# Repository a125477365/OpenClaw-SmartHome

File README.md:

# OpenClaw Smart Home System

## Overview

This repository provides a complete design for a smart home system built on the OpenClaw platform. It consists of:

- **1 Skill**: `HomeSkill` (container for plugins)
- **2 Plugins**:
  1. `DeviceLinkPlugin` – handles device connection, ECDH pairing, encryption, control, and status reporting
  2. `UIManagePlugin` – provides a web-based management interface (HTTPS with password auth, auto port selection)
- **1 Data file**: `devices.json` – stores device info, state, and encryption keys
- **Hardware design**: ESP32-based smart switch

All code and documentation are in English.

## Security Features

### ECDH-Based Pairing (Bluetooth-Style)

- **No pre-shared secrets**: Each device generates its own EC key pair
- **User confirmation**: 6-digit confirmation code prevents MITM attacks
- **Forward secrecy**: New session keys for each pairing
- **AES-256-GCM encryption**: Authenticated encryption for all communications

### UI Security

- **Password protected**: Strong password required for web access
- **HTTPS only**: HTTP redirects to HTTPS
- **Session management**: 24-hour session timeout
- **Password hashing**: PBKDF2-SHA512 with 100,000 iterations

## Directory Structure

```
OpenClaw-SmartHome/
├── README.md
├── Skills/
│   └── HomeSkill/
│       ├── openclaw.skill.json
│       ├── package.json              # npm dependencies
│       ├── devices.json
│       ├── DeviceLinkPlugin/
│       │   ├── openclaw.plugin.json
│       │   ├── config.json
│       │   └── index.js              # Main plugin code
│       └── UIManagePlugin/
│           ├── openclaw.plugin.json
│           ├── config.json
│           ├── index.js              # HTTPS server
│           ├── password.json         # Stored password hash
│           ├── ssl/
│           │   ├── cert.pem
│           │   └── key.pem
│           └── web/
│               ├── index.html
│               └── edit.html
├── docs/
│   ├── hardware-design.md
│   ├── security-design.md
│   └── software-design.md
└── firmware/
    └── esp32_switch/
        └── esp32_switch.ino
```

## Tools Provided

### DeviceLinkPlugin

| Tool | Description |
|------|-------------|
| `device.control` | Send control command (on/off/query) |
| `device.pairing.start` | Initiate ECDH pairing process |
| `device.pairing.confirm` | Complete pairing after user confirms code |
| `device.pairing.reject` | Reject pending pairing |
| `device.reconnect` | Reconnect using stored public key |
| `device.unauthorize` | Revoke device authorization |
| `device.delete` | Remove device completely |
| `device.sync` | Query and update device state |
| `device.list` | List all registered devices |

### UIManagePlugin

| Tool | Description |
|------|-------------|
| `ui.password.get` | Get password info (cannot view, only reset) |
| `ui.password.reset` | Generate new random password |
| `ui.ports` | Get actual HTTP/HTTPS ports in use |

## Configuration

### Auto Port Selection

Both plugins support automatic port selection:

1. Tries configured port first
2. If occupied, searches for next available port
3. Search range configurable via `portRangeMin` and `portRangeMax`

### DeviceLinkPlugin/config.json

```json
{
  "devicePort": 8080,
  "mdnsPort": 5353,
  "pairingTimeout": 60000,
  "portRangeMin": 8080,
  "portRangeMax": 8100,
  "enableMdnsDiscovery": false,
  "encryption": {
    "algorithm": "aes-256-gcm",
    "keyLength": 32,
    "ivLength": 12
  }
}
```

### UIManagePlugin/config.json

```json
{
  "httpsPort": 8083,
  "httpPort": 8082,
  "portRangeMin": 8080,
  "portRangeMax": 8100,
  "webRoot": "./web",
  "ssl": {
    "key": "./ssl/key.pem",
    "cert": "./ssl/cert.pem"
  }
}
```

## Quick Start

1. Clone this repository into your OpenClaw `Skills/` directory:
   ```bash
   git clone https://github.com/your-org/OpenClaw-SmartHome.git ~/.openclaw/skills/HomeSkill
   ```

2. Install dependencies:
   ```bash
   cd ~/.openclaw/skills/HomeSkill
   npm install
   ```

3. Restart OpenClaw (skills load automatically)

4. Access the UI:
   - HTTPS: `https://localhost:8083` (or next available port)
   - Check logs for initial password: `ui.password.reset` to get a new one

5. Pair a device:
   ```
   User: I found a new device, start pairing
   Agent: [calls device.pairing.start]
   Agent: Please confirm code 123456 matches the device
   User: Confirmed
   Agent: [calls device.pairing.confirm]
   ```

## Pairing Flow

```
┌─────────────┐                    ┌─────────────┐
│   Device    │                    │  OpenClaw   │
└──────┬──────┘                    └──────┬──────┘
       │                                  │
       │ pairing_request                  │
       │ {deviceId, publicKey}            │
       │─────────────────────────────────>│
       │                                  │
       │                Compute shared secret
       │                Generate 6-digit code
       │                                  │
       │ pairing_response                 │
       │ {ephemeralPublicKey, salt}       │
       │<─────────────────────────────────│
       │                                  │
       │    [User confirms code matches]  │
       │                                  │
       │ pairing_confirm                  │
       │ {confirmed: true}                │
       │─────────────────────────────────>│
       │                                  │
       │ pairing_success                  │
       │<─────────────────────────────────│
       │                                  │
```

## Hardware Design

See `docs/hardware-design.md` for:
- ESP32-WROOM-32D based smart switch
- Relay module (5V, opto-isolated)
- PCB layout and BOM
- Assembly instructions

## Security Design

See `docs/security-design.md` for:
- ECDH pairing details
- AES-256-GCM encryption
- Replay attack protection
- Production security recommendations

## Software Design

See `docs/software-design.md` for:
- Architecture diagrams
- Communication protocol
- API specifications
- Data structures

## Firmware

See `firmware/esp32_switch/esp32_switch.ino` for:
- ESP32 Arduino firmware
- ECDH key generation
- AES-256-GCM encryption
- WiFi SmartConfig provisioning

## License

MIT

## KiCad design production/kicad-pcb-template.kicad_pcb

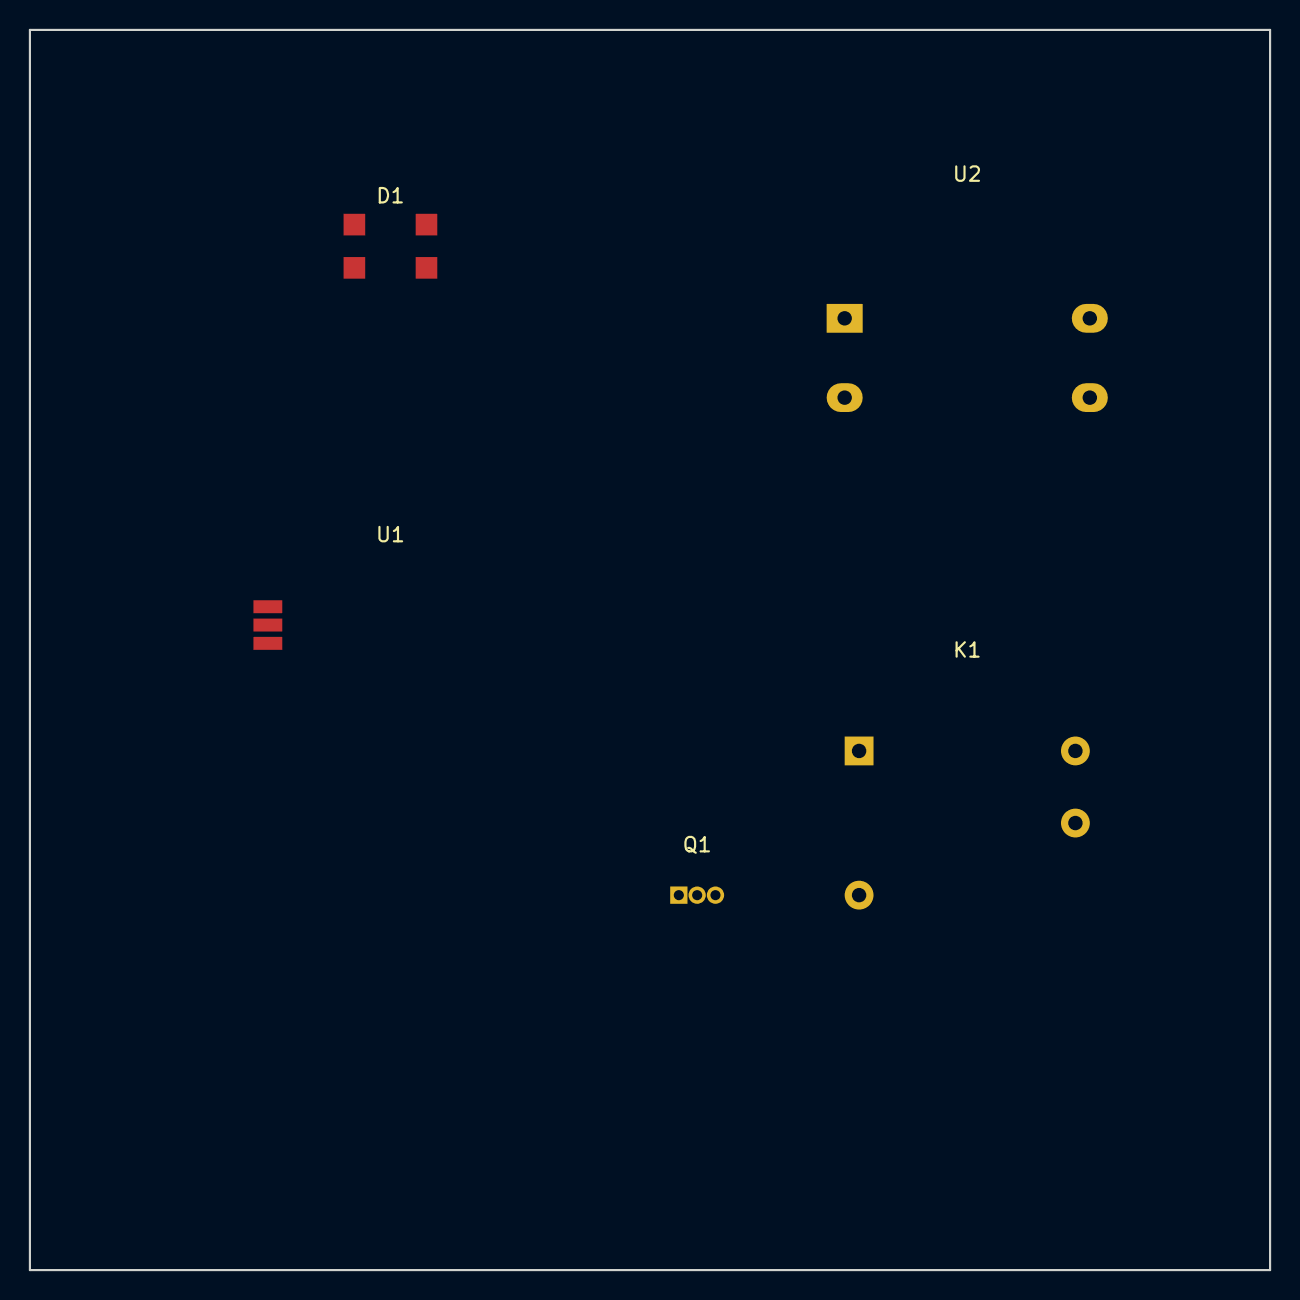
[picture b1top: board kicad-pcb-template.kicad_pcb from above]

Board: 2 copper layers, 86.0 x 86.0 mm, 5 parts (0 on the bottom side), 3 nets, no tracks yet.

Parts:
D1: WS2812B; LED_WS2812B_PLCC4_5.0x5.0mm_P3.10mm
K1: SRD-05VDC-SL-C; Relay_SPST_SRD-05VDC
Q1: S8050; TO-92_Inline
U1: ESP32-WROOM-32D
U2: HLK-PM01; Converter_ACDC_HiLink_HLK-PM01

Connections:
+5V: D1.1, K1.1, U2.3
AC-L: K1.5, U2.1
GND: D1.3, U1.2, U2.4

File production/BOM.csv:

物料清单 (BOM)
OpenClaw智能开关 v1.0

序号,类别,名称,型号/规格,数量,单价(RMB),总价(RMB),供应商,备注
1,主控,ESP32模块,ESP32-WROOM-32D 4MB Flash,1,18,18,立创/淘宝,核心主控
2,继电器,功率继电器,SRD-05VDC-SL-C 常闭型 10A,1,4,4,立创,关键：常闭型！
3,光耦,光电耦合器,PC817 4脚直插,1,0.5,0.5,立创,继电器隔离驱动
4,三极管,NPN三极管,S8050 TO-92,1,0.1,0.1,立创,继电器驱动
5,二极管,整流二极管,1N4007 1A 1000V,1,0.05,0.05,立创,续流保护
6,电源,AC-DC模块,HLK-PM01 220V转5V 1A,1,10,10,淘宝,金升阳原厂
7,电容,电解电容,100μF/10V 105℃,1,0.3,0.3,立创,电源滤波
8,电容,陶瓷电容,0.1μF 50V 0805,3,0.05,0.15,立创,去耦电容
9,LED,RGB LED,WS2812B 5050封装,1,0.8,0.8,淘宝,状态指示灯
10,开关,轻触开关,6x6x5mm 四脚直插,1,0.1,0.1,立创,配网按钮
11,端子,接线端子,KF301-2P 5.08mm 绿色,4,0.5,2,立创,L/N/SW/COM接线
12,电阻,碳膜电阻,220Ω 1/4W,1,0.02,0.02,立创,LED限流
13,电阻,碳膜电阻,1KΩ 1/4W,2,0.02,0.04,立创,三极管基极
14,电阻,碳膜电阻,10KΩ 1/4W,2,0.02,0.04,立创,按钮上拉
15,保险,保险丝,250V 1A 5x20mm,1,0.2,0.2,立创,过流保护
16,保险,保险丝座,5x20mm 直插,1,0.3,0.3,立创,配合保险丝
17,压敏,压敏电阻,14D471K 470V,1,0.3,0.3,立创,浪涌保护
18,排母,排母座,2.54mm 19P 直插,1,0.5,0.5,立创,ESP32接口
19,PCB,电路板,86x86mm 双面 FR-4 1.6mm,1,12,12,嘉立创,打样5片起
20,外壳,上盖,PC阻燃 86型,1,4,4,注塑厂,需开模
21,外壳,下盖,PC阻燃 86型,1,4,4,注塑厂,需开模
22,包装,彩盒,90x90x40mm,1,1.5,1.5,印刷厂,
23,包装,说明书,A5折叠,1,0.5,0.5,印刷厂,
24,包装,保修卡,A6,1,0.2,0.2,印刷厂,
25,包装,合格证,50x30mm,1,0.05,0.05,印刷厂,

,,,,,,,,
小计(电子元件),,,,,,36.45,
小计(PCB),,,,,,12,
小计(外壳),,,,,,8,
小计(包装),,,,,,2.25,
总计(单件成本),,,,,,58.7,,

备注：
1. 常闭型继电器是关键！断电时触点闭合，传统开关可正常使用
2. 电源模块建议用金升阳HLK系列，质量稳定
3. ESP32模块可选用ESP32-WROOM-32E（外置天线）或32D（内置天线）
4. 量产1000件以上成本可降至45-50元/件
5. 所有价格仅供参考，以实际采购为准

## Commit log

2026-03-21 Initial commit: OpenClaw Smart Home system with DeviceLinkPlugin and UIManagePlugin
2026-03-21 Add ESP32 firmware and security design documentation
2026-03-21 Add HTTPS support to UIManagePlugin (self-signed certificate fallback to HTTP)
2026-03-21 Update UIManagePlugin to serve HTTPS with self-signed certs, redirect HTTP to HTTPS
2026-03-21 Add HTTPS support to UIManagePlugin with self-signed certificate and HTTP redirect; update README
2026-03-21 Add password protection to UIManagePlugin with login page and password reset functionality
    - Added login page with secure password authentication
    - Implemented session management with 24-hour timeout
    - Added password reset functionality (generates strong random passwords)
    - Registered ui.password.get and ui.password.reset tools (only main session should call)
    - Updated plugin version to 1.1.0
    - Password stored securely with PBKDF2 hashing
2026-03-21 Fix all identified issues:
    1. Fixed encryption algorithm mismatch (AES-256-CBC -> AES-256-GCM)
    2. Implemented ECDH-based pairing flow (Bluetooth-style)
    3. Added device discovery via mDNS (optional for public cloud)
    4. Added reconnection flow using stored public keys
    5. Implemented auto port selection with fallback
    6. Added software-design.md documentation
2026-03-21 Set enableMdnsDiscovery to false by default (public cloud deployment friendly)
2026-03-22 Fix ECDH curve mismatch: change ESP32 from Curve25519 to P-256 (secp256r1) to match OpenClaw side
2026-03-22 Fix all remaining issues:
    1. UIManagePlugin: HTTP server now uses actualHttpPort (auto port selection)
    2. ESP32: Added missing mbedtls/base64.h and mbedtls/md.h headers
    3. ESP32: Fixed typo WianoClient -> WiFiClient in handlePairingConfirm
    4. Key derivation: Changed OpenClaw to use simple SHA256 matching ESP32 implementation
    All critical bugs fixed, ECDH pairing should now work correctly.
2026-03-22 Add automated tests: 12 crypto tests + 7 integration tests
    All 19 tests pass:
    - ECDH key generation and shared secret
    - Session key derivation (SHA256)
    - AES-256-GCM encryption/decryption
    - Confirmation code generation
    - End-to-end pairing simulation
2026-03-22 Add WiFi provisioning firmware with web-based configuration
    Features:
    - Device starts in AP mode (access point)
    - User connects to device WiFi and opens http://192.168.4.1
    - Web page shows WiFi scan results with signal strength
    - User selects WiFi, enters password and OpenClaw server address
    - Device connects to WiFi and OpenClaw server
2026-03-22 Fix WiFi provisioning: switch to STA-only mode after pairing
    Key changes:
    - After pairing confirmed, device saves config and restarts
    - Normal mode: WiFi STA only (no AP hotspot)
    - Provisioning mode: WiFi AP only for first-time setup
    - Added button reset: hold 5s to clear config and restart
    - Uses Preferences (NVS) for persistent storage
2026-03-22 Add manual WiFi input option for iOS compatibility
    iOS cannot scan WiFi networks directly, so add:
    - Two tabs: '手动输入' (manual) and '扫描列表' (scan list)
    - Manual input as default for iOS users
    - Warning box explaining iOS steps to scan WiFi
    - Android/Desktop users can still use scan list feature
2026-03-22 Consolidate firmware: merge provisioning into main file
    - Remove separate esp32_switch_provisioning.ino
    - All functionality now in esp32_switch.ino
    - Single firmware handles both provisioning and normal mode
2026-03-22 Add comprehensive end-to-end tests
    Tests cover full flow from device provisioning to smart control:
    - Phase 1: Device Provisioning (MAC ID, EC key pair, AP mode)
    - Phase 2: ECDH Pairing (Bluetooth-style, 6-digit code)
    - Phase 3: Device Control (ON/OFF/Query commands)
    - Phase 4: Web UI Auth (PBKDF2, session management)
    - Phase 5: Full Round-trip (pair -> control -> query)
2026-03-22 Complete hardware design for 86-type smart switch
    Features:
    - Fits standard 86-type wall switch box
    - Preserves original manual switch functionality
    - Normally-closed relay: works even when smart module is off
    - Single button design with status LED and reset button
    - Clear wiring diagrams for installation
2026-03-22 Add complete production package for manufacturer
    Files added:
    - production/生产制造指南.md - Complete manufacturing guide
    - production/BOM.csv - Bill of Materials with prices
    - production/测试标准.md - Quality test standards
    - production/采购清单.md - Sourcing and procurement guide
    Includes:
2026-03-22 Add comprehensive sample diagrams for smart switch
    Includes:
    - Circuit schematic diagram
    - ESP32 pin connection diagram
    - Physical wiring diagram
    - PCB layout reference
    - Enclosure panel design
2026-03-22 Add product image design guide and AI generation prompts
    Includes:
    - Detailed product appearance description
    - Midjourney/DALL-E prompts for rendering
    - Photography requirements for product shots
    - Packaging design suggestions
    - Designer hiring guide and templates
2026-03-22 Add detailed circuit schematic for PCB design
    Includes:
    - Complete circuit schematic (ASCII art)
    - Power supply circuit (HLK-PM01)
    - ESP32 main controller connections
    - Relay driver circuit (with normally-closed relay)
    - Configuration button circuit
2026-03-22 Add complete production files for manufacturing
    Generated all missing files:
    1. pcb-design.json - PCB layout specification
    2. product-spec.json - Product specifications
    3. gerber-guide.md - How to generate Gerber files
    4. enclosure-spec.md - 3D enclosure specifications
    Now includes complete production package:
2026-03-22 Add quick generation guide and EasyEDA template
    Created practical guides for users who cannot generate binary files:
    - 快速生成指南.md: Three lazy approaches (Taobao outsourcing, EasyEDA DIY, ready-made modules)
    - easyeda-project-template.json: Template for EasyEDA import
    Recommendations based on user needs:
    - Quick verification: Buy ESP32 relay module (~50 RMB)
    - Small batch: Taobao PCB service (200-500 RMB)
2026-03-22 Add STL file for 3D printing enclosure
    Generated ASCII STL file with:
    - Top cover with LED hole (3mm) and button hole (8mm)
    - Bottom cover with 4 terminal holes (L/N/COM/SW)
    - Standard 86mm x 86mm dimensions
    - Mounting holes at 60.3mm spacing
    Ready for 3D printing (PLA/PETG recommended)
2026-03-22 Add KiCad and Altium Designer templates/scripts
    Generated:
    - kicad-pcb-template.kicad_pcb - KiCad PCB template with all components
    - kicad-schematic-template.kicad_sch - KiCad schematic template
    - altium-project-template.PrjPcb - Altium project file
    - altium-create-script.vbs - Altium VBScript to create schematic and PCB
    Users can now:
2026-03-22 Add complete Gerber files for PCB manufacturing
    Found and copied existing Gerber files from previous session:
    - OpenClaw-SmartSwitch-v2-F.Cu.gtl (顶层铜箔)
    - OpenClaw-SmartSwitch-v2-B.Cu.gbl (底层铜箔)
    - OpenClaw-SmartSwitch-v2-F.Mask.gts (顶层阻焊)
    - OpenClaw-SmartSwitch-v2-B.Mask.gbs (底层阻焊)
    - OpenClaw-SmartSwitch-v2-F.SilkS.gto (顶层丝印)
2026-03-22 Generate complete Gerber v3 files matching all requirements
    ✅ Correct specifications:
    - ESP32-WROOM-32D (not ESP32-C3)
    - SRD-05VDC-SL-C Normally Closed relay
    - Mounting holes: 60mm spacing (13,73 positions)
    - Strong-weak separation at X=45mm with >=6mm clearance
    - WS2812B LED at top center (25, 15)
